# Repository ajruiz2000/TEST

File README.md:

# TEST
This is test repisotory for QFI

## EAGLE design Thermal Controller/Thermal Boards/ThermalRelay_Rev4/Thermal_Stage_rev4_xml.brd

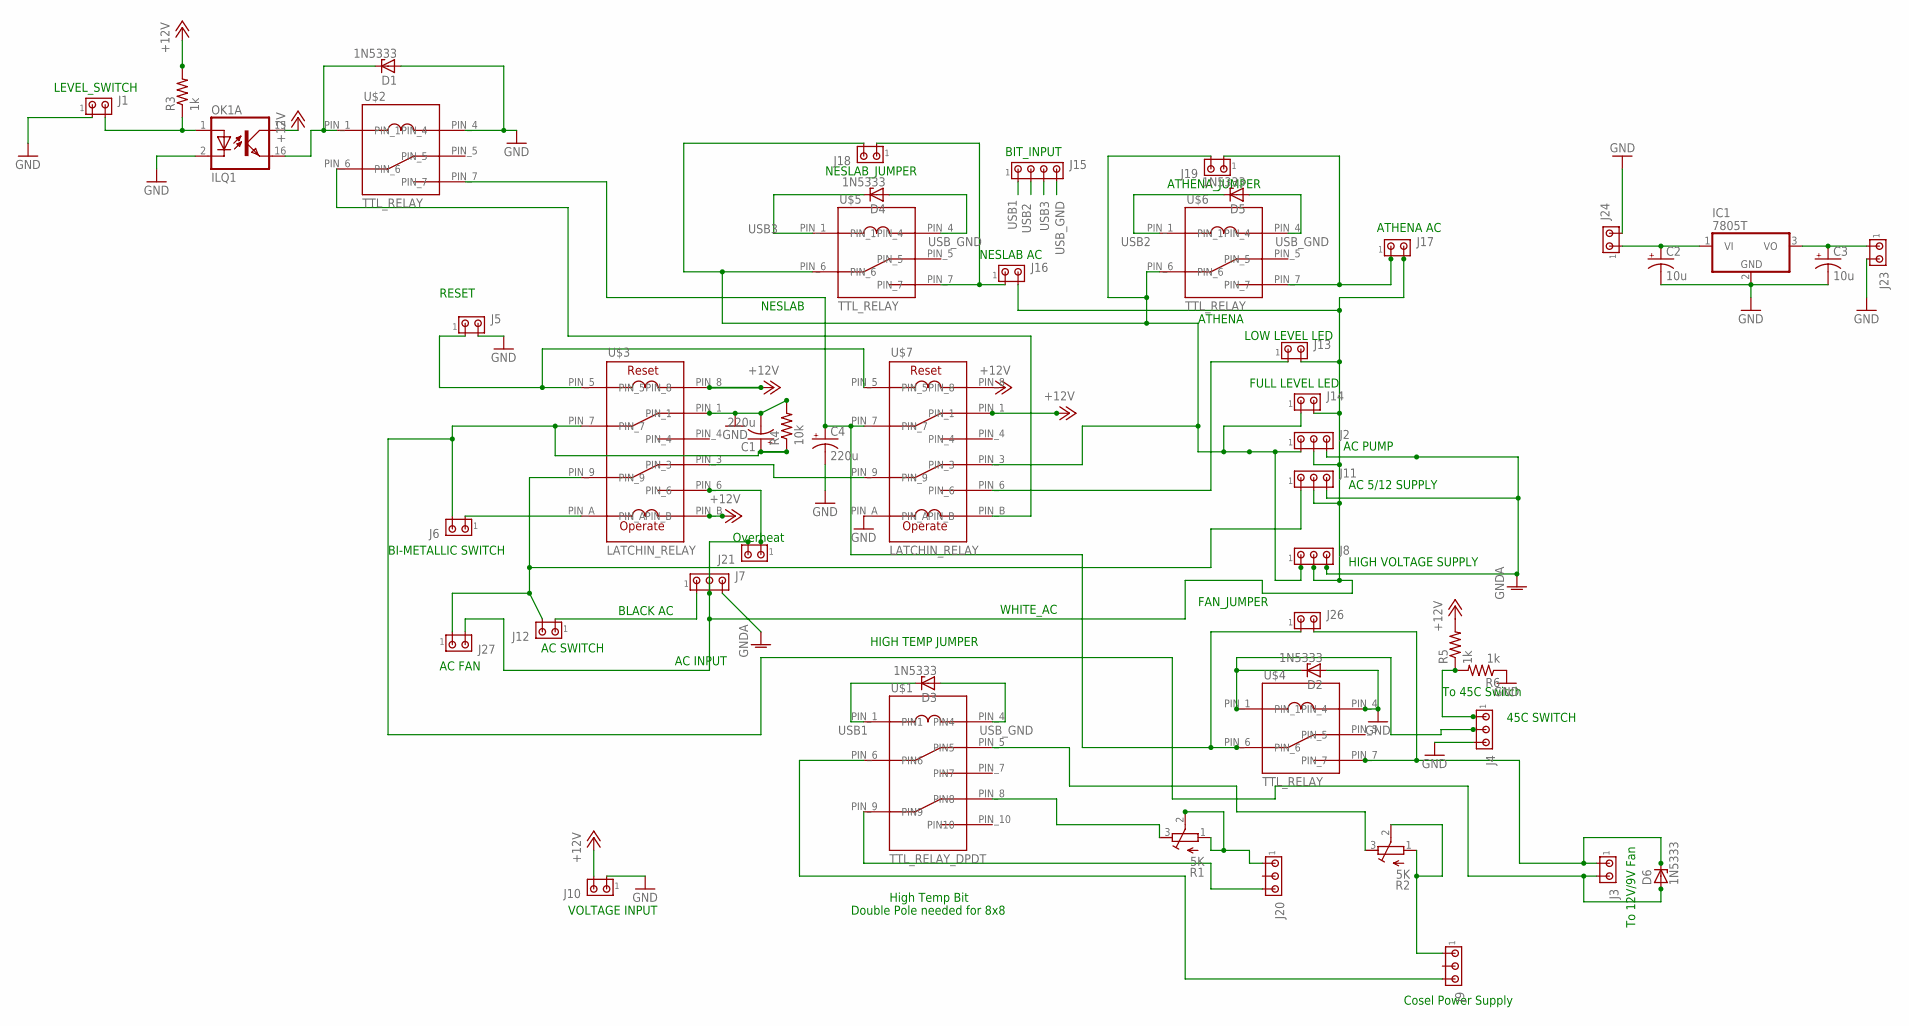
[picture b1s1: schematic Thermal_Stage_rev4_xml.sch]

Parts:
C1, C4: 220u; E5-13
C2, C3: 10u; E2,5-6E
D1, D2, D3, D4, D5, D6: 1N5333; C1702-15
IC1: 7805T; TO220H
J1, J3, J5, J6, J10, J12, J13, J14, J16, J17, J21, J27: MTA02-156; 1X2MTA
J2, J4, J7, J8, J11: MTA03-156; 1X3MTA
J9, J20: MTA03-100; 10X03MTA
J15: MTA04-100; 10X04MTA
J18, J19, J23, J24, J26: MTA02-100; 10X02MTA
OK1: ILQ1; DIL16
R1, R2: 5K; RTRIM3296W
R3, R5, R6: 1k; 0204/7
R4: 10k; 0204/7
U$1: TTL_RELAY_DPDT
U$2, U$4, U$5, U$6: TTL_RELAY; R1OS-E1Y1-J1.0K
U$3, U$7: LATCHIN_RELAY; 785XBXCD-12D

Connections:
+12V: J10.2, OK1.15 (COL), R3.2, R5.2, U$3.PIN_8, U$3.PIN_B, U$7.PIN_1, U$7.PIN_8
BLACK_AC: J7.1, J12.1
BLACK_AC_SWITCH: C1.+, D6.A, J3.2, J6.2, R4.1, U$3.PIN_7
GND: C1.-, C2.-, C3.-, C4.-, D1.A, D2.A, IC1.2 (GND), J1.1, J4.3, J5.2, J10.1, J23.2, J24.2, OK1.2 (C), R4.2, R6.1, U$2.PIN_4, U$3.PIN_1, U$4.PIN_4, U$7.PIN_A
GNDA: J2.3, J7.3, J8.3, J11.3
unnamed: D6.C, J3.1, J26.2, U$4.PIN_7
unnamed: J21.1, U$3.PIN_6
unnamed: J20.1, R1.1 (E), R1.2 (S)
unnamed: J5.1, U$3.PIN_5, U$7.PIN_5
unnamed: U$2.PIN_6, U$7.PIN_B
unnamed: J11.1, J12.2, J27.1, U$3.PIN_9
unnamed: R1.3 (A), U$1.PIN_8 (PIN8)
unnamed: D1.C, OK1.16 (EMIT), U$2.PIN_1
unnamed: J13.1, U$7.PIN_6
unnamed: J1.2, OK1.1 (A), R3.1
unnamed: C4.+, J26.1, U$2.PIN_7, U$4.PIN_6, U$7.PIN_7
unnamed: J2.1, J8.1, J14.1, J18.2, J19.2, U$5.PIN_6, U$6.PIN_6, U$7.PIN_3
unnamed: J9.3, U$1.PIN_6 (PIN6)
unnamed: J17.1, J19.1, U$6.PIN_7
unnamed: J16.1, J18.1, U$5.PIN_7
unnamed: D2.C, J4.2, U$4.PIN_1
unnamed: U$3.PIN_3, U$7.PIN_9
unnamed: J20.3, U$1.PIN_9 (PIN9)
unnamed: J4.1, R5.1, R6.2
unnamed: R2.3 (A), U$1.PIN_5 (PIN5)
unnamed: J9.1, R2.1 (E), R2.2 (S)
unnamed: C2.+, IC1.1 (VI), J24.1
unnamed: C3.+, IC1.3 (VO), J23.1
unnamed: J6.1, U$3.PIN_A
USB1: D3.C, J15.1, U$1.PIN_1 (PIN1)
USB2: D5.C, J15.2, U$6.PIN_1
USB3: D4.C, J15.3, U$5.PIN_1
USB_GND: D3.A, D4.A, D5.A, J15.4, U$1.PIN_4 (PIN4), U$5.PIN_4, U$6.PIN_4
WHITE_AC: J2.2, J7.2, J8.2, J11.2, J13.2, J14.2, J16.2, J17.2, J21.2, J27.2

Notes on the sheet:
BI-METALLIC SWITCH
RESET
AC SWITCH
AC INPUT
LEVEL_SWITCH
LOW LEVEL LED
FULL LEVEL LED
AC PUMP
AC 5/12 SUPPLY
ATHENA AC
HIGH VOLTAGE SUPPLY
WHITE_AC
45C SWITCH
BLACK AC
VOLTAGE INPUT
Cosel Power Supply
High Temp Bit
BIT_INPUT
ATHENA_JUMPER
ATHENA
NESLAB
NESLAB AC
NESLAB_JUMPER
HIGH TEMP JUMPER
FAN_JUMPER
To 12V/9V Fan
To 45C Switch
AC FAN
Double Pole needed for 8x8
Overheat

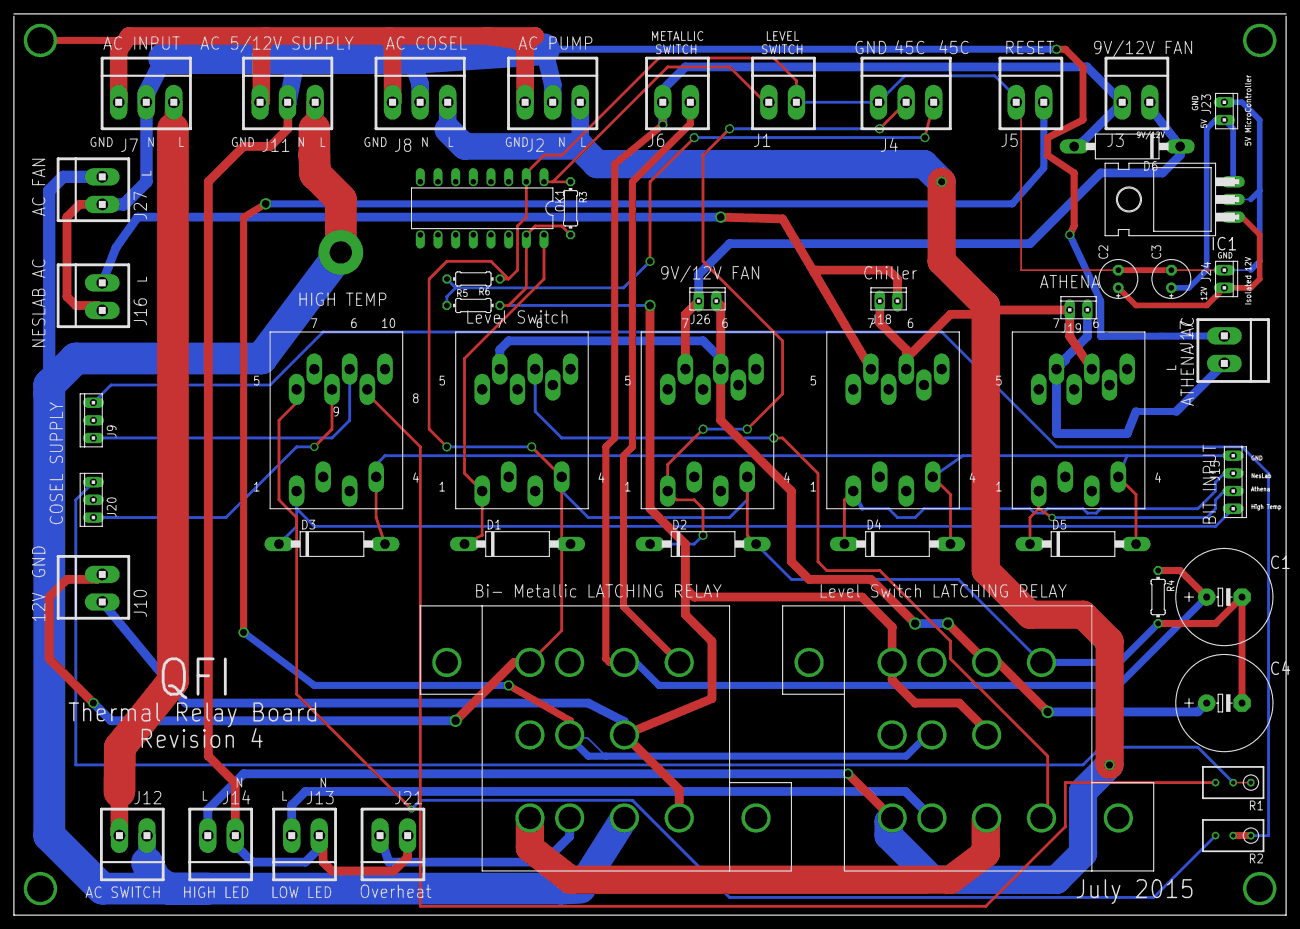
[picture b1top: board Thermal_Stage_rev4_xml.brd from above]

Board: 2 copper layers, 182.9 x 129.5 mm, 50 parts (0 on the bottom side), 34 nets.

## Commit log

2017-07-06 Add files via upload
    Added PST .sch and .brd files
2017-07-06 Create PST
2017-07-06 Create p
2018-05-01 XIVA Dark Cloth
    Initial Commit
2018-05-08 PST Rev 9
    PST Revision 9 modification document
2018-05-08 PST Version 10
    Eagle Files, Schematics, BOM, firmware and document set
2018-05-22 Add files via upload
    Added BOM
2024-01-08 push up thermal and TMTD (changes till need to be made)
